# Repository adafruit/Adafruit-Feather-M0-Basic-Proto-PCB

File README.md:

## Adafruit Feather M0 Basic Proto PCB
<a href="http://www.adafruit.com/products/2772"><br/>
Click here to purchase one from the Adafruit shop</a>

The Feather M0 has an ATSAMD21G18 ARM Cortex M0 processor, clocked at 48 MHz and at 3.3V logic, the same one used in the Arduino Zero. This chip has a whopping 256K of FLASH (8x more than the Atmega328 or 32u4) and 32K of RAM (16x as much)! This chip comes with built in USB so it has USB-to-Serial program & debug capability built in with no need for an FTDI-like chip.

To make it easy to use for portable projects, we added a connector for any of our 3.7V Lithium polymer batteries and built in battery charging. You don't need a battery, it will run just fine straight from the micro USB connector. But, if you do have a battery, you can take it on the go, then plug in the USB to recharge. The Feather will automatically switch over to USB power when its available. We also tied the battery thru a divider to an analog pin, so you can measure and monitor the battery voltage to detect when you need a recharge.

PCB files for the Adafruit Feather M0 Basic Proto. The format is EagleCAD schematic and board layout
- https://www.adafruit.com/product/2772

### License

Adafruit invests time and resources providing this open source design, please support Adafruit and open-source hardware by purchasing products from [Adafruit](https://www.adafruit.com)!

All text above must be included in any redistribution

Designed by Limor Fried/Ladyada for Adafruit Industries.
Creative Commons Attribution/Share-Alike, all text above must be included in any redistribution. 
See license.txt for additional information.

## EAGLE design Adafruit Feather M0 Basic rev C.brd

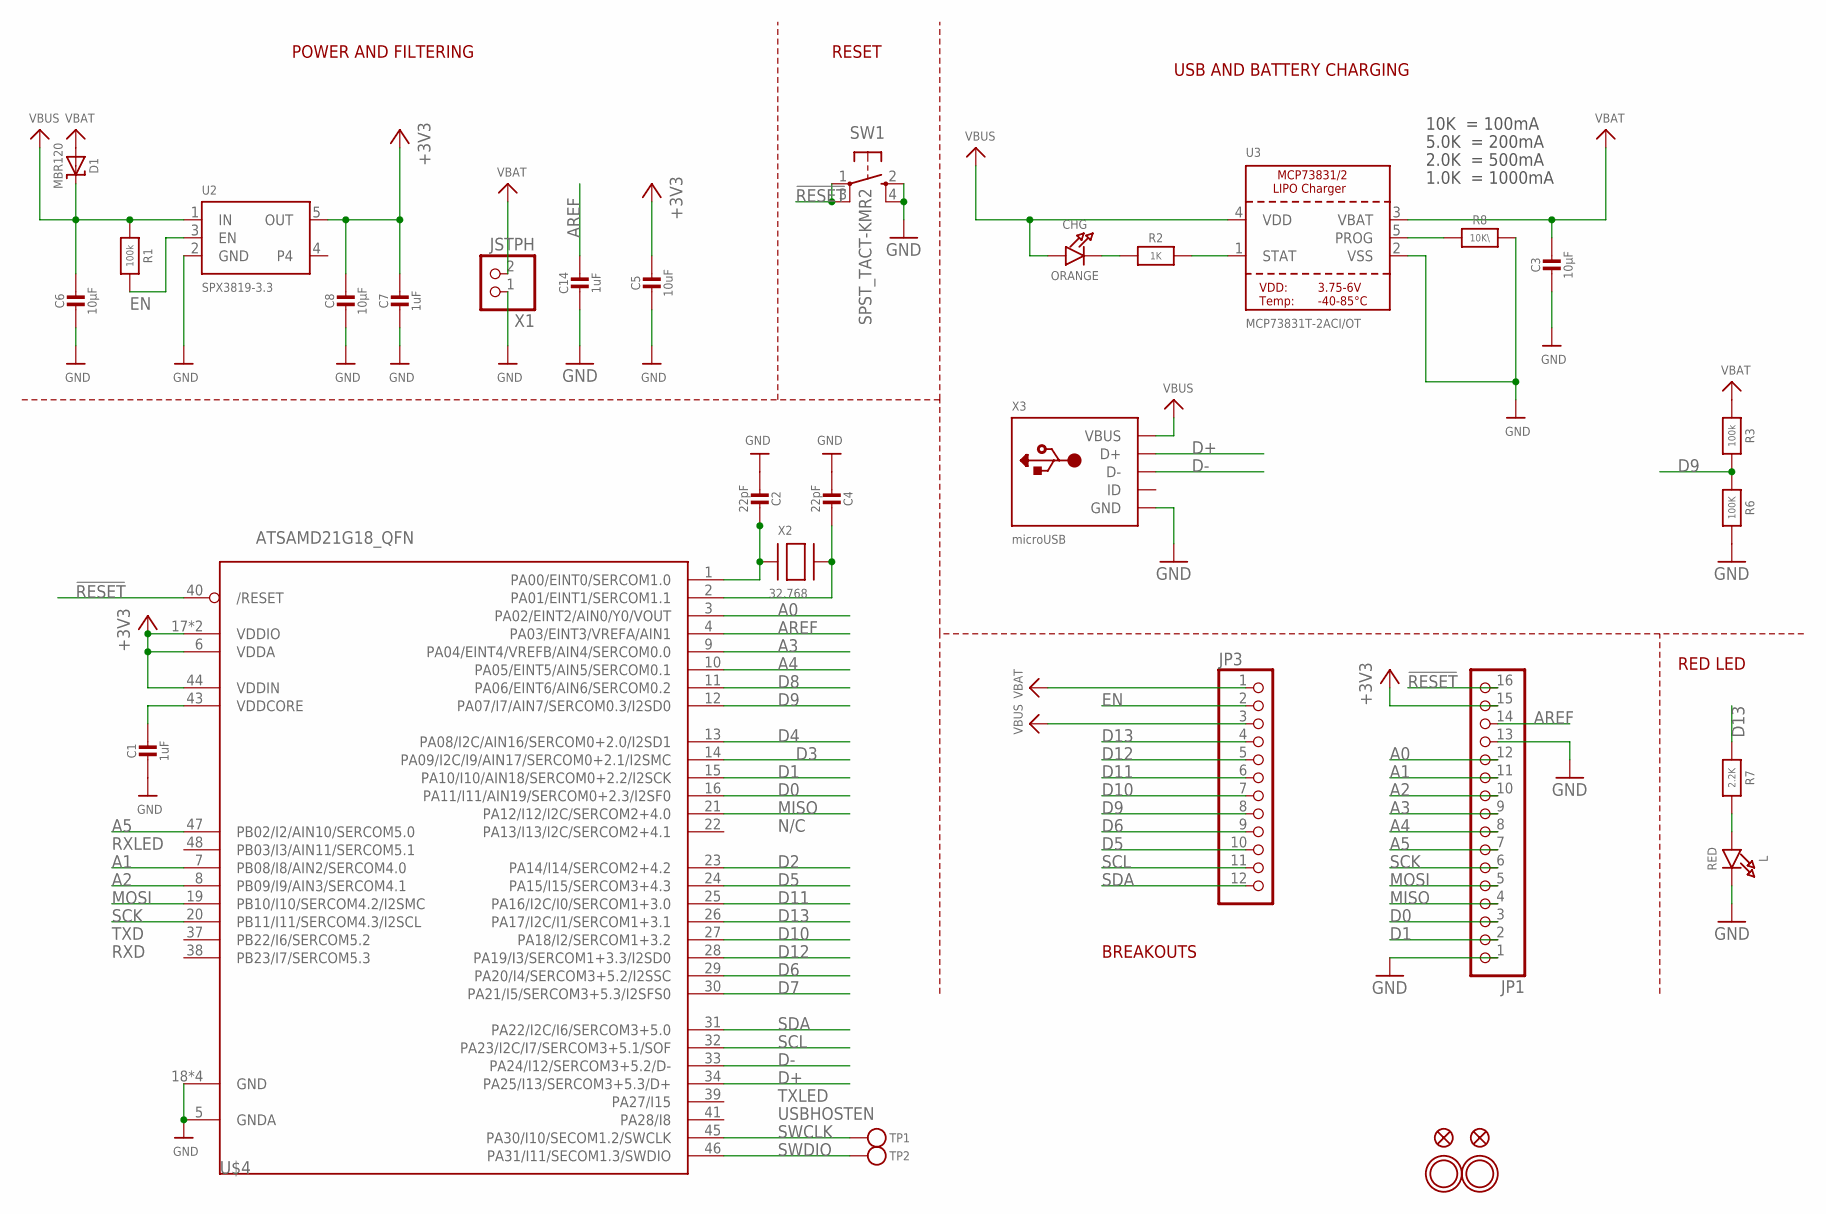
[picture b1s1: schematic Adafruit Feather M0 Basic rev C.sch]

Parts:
C1, C7, C14: 1uF; 0603-NO
C2, C4: 22pF; 0603-NO
C3, C6, C8: 10µF; 0805-NO
C5: 10uF; 0805-NO
CHG: ORANGE; CHIPLED_0805_NOOUTLINE
D1: MBR120; SOD-123
JP1: HEADER-1X16ROUND; 1X16_ROUND
JP3: HEADER-1X12; 1X12_ROUND
L: RED; CHIPLED_0805_NOOUTLINE
R1, R3: 100k; 0603-NO
R2: 1K; 0603-NO
R6: 100K; 0603-NO
R7: 2.2K; 0603-NO
R8: 10K\; 0603-NO
SW1: SPST_TACT-KMR2; KMR2
TP1, TP2: TESTPOINTROUND1.5MM; TESTPOINT_ROUND_1.5MM
U2: SPX3819-3.3; SOT23-5
U3: MCP73831T-2ACI/OT; SOT23-5
U$4: ATSAMD21G18_QFN; TQFN48_7MM
U$31, U$32: MOUNTINGHOLE2.5; MOUNTINGHOLE_2.5_PLATED
U$34, U$35: FIDUCIAL""; FIDUCIAL_1MM
X1: JSTPH; JSTPH2
X2: 32.768; XTAL3215
X3: microUSB; 4UCONN_20329_V2

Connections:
!RESET: JP1.16, SW1.1, SW1.3 (P1), U$4.40 (/RESET)
+3V3: C5.1, C7.1, C8.1, JP1.15, U2.5 (OUT), U$4.6 (VDDA), U$4.17 (VDDIO), U$4.36 (VDDIO), U$4.44 (VDDIN)
A0: JP1.12, U$4.3 (PA02/EINT2/AIN0/Y0/VOUT)
A1: JP1.11, U$4.7 (PB08/I8/AIN2/SERCOM4.0)
A2: JP1.10, U$4.8 (PB09/I9/AIN3/SERCOM4.1)
A3: JP1.9, U$4.9 (PA04/EINT4/VREFB/AIN4/SERCOM0.0)
A4: JP1.8, U$4.10 (PA05/EINT5/AIN5/SERCOM0.1)
A5: JP1.7, U$4.47 (PB02/I2/AIN10/SERCOM5.0)
AREF: C14.1, JP1.14, U$4.4 (PA03/EINT3/VREFA/AIN1)
D0: JP1.3, U$4.16 (PA11/I11/AIN19/SERCOM0+2.3/I2SF0)
D1: JP1.2, U$4.15 (PA10/I10/AIN18/SERCOM0+2.2/I2SCK)
D2: U$4.23 (PA14/I14/SERCOM2+4.2)
D3: U$4.14 (PA09/I2C/I9/AIN17/SERCOM0+2.1/I2SMC)
D4: U$4.13 (PA08/I2C/AIN16/SERCOM0+2.0/I2SD1)
D5: JP3.10, U$4.24 (PA15/I15/SERCOM3+4.3)
D6: JP3.9, U$4.29 (PA20/I4/SERCOM3+5.2/I2SSC)
D7: U$4.30 (PA21/I5/SERCOM3+5.3/I2SFS0)
D8: U$4.11 (PA06/EINT6/AIN6/SERCOM0.2)
D9: JP3.8, R3.2, R6.1, U$4.12 (PA07/I7/AIN7/SERCOM0.3/I2SD0)
D10: JP3.7, U$4.27 (PA18/I2/SERCOM1+3.2)
D11: JP3.6, U$4.25 (PA16/I2C/I0/SERCOM1+3.0)
D12: JP3.5, U$4.28 (PA19/I3/SERCOM1+3.3/I2SD0)
D13: JP3.4, R7.1, U$4.26 (PA17/I2C/I1/SERCOM1+3.1)
D+: U$4.34 (PA25/I13/SERCOM3+5.3/D+), X3.D+
D-: U$4.33 (PA24/I12/SERCOM3+5.2/D-), X3.D-
EN: JP3.2, R1.2, U2.3 (EN)
GND: C1.2, C2.2, C3.2, C4.2, C5.2, C6.2, C7.2, C8.2, C14.2, JP1.1, JP1.13, L.C, R6.2, R8.2, SW1.2 (S), SW1.4 (S1), U2.2 (GND), U3.2 (VSS), U$4.5 (GNDA), U$4.18 (GND), U$4.35 (GND), U$4.42 (GND), U$4.THERMAL (GND), X1.1, X3.BASE@1 (GND), X3.BASE@2 (GND), X3.GND, X3.SPRT@1 (GND), X3.SPRT@2 (GND), X3.SPRT@3 (GND), X3.SPRT@4 (GND)
MISO: JP1.4, U$4.21 (PA12/I12/I2C/SERCOM2+4.0)
MOSI: JP1.5, U$4.19 (PB10/I10/SERCOM4.2/I2SMC)
unnamed: CHG.C, R2.1
unnamed: L.A, R7.2
unnamed: R2.2, U3.1 (STAT)
unnamed: R8.1, U3.5 (PROG)
unnamed: C2.1, U$4.1 (PA00/EINT0/SERCOM1.0), X2.P$1
unnamed: C4.1, U$4.2 (PA01/EINT1/SERCOM1.1), X2.P$2
SCK: JP1.6, U$4.20 (PB11/I11/SERCOM4.3/I2SCL)
SCL: JP3.11, U$4.32 (PA23/I2C/I7/SERCOM3+5.1/SOF)
SDA: JP3.12, U$4.31 (PA22/I2C/I6/SERCOM3+5.0)
SWCLK: TP1.P$1, U$4.45 (PA30/I10/SECOM1.2/SWCLK)
SWDIO: TP2.P$1, U$4.46 (PA31/I11/SECOM1.3/SWDIO)
VBAT: C3.1, D1.A, JP3.1, R3.1, U3.3 (VBAT), X1.2
VBUS: C6.1, CHG.A, D1.C, JP3.3, R1.1, U2.1 (IN), U3.4 (VDD), X3.VBUS
VDDCORE: C1.1, U$4.43 (VDDCORE)

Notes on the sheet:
POWER AND FILTERING
RESET
10K = 100mA
5.0K = 200mA
2.0K = 500mA
1.0K = 1000mA
N/C
TXLED
USBHOSTEN
RXLED
TXD
RXD
USB AND BATTERY CHARGING
BREAKOUTS
RED LED

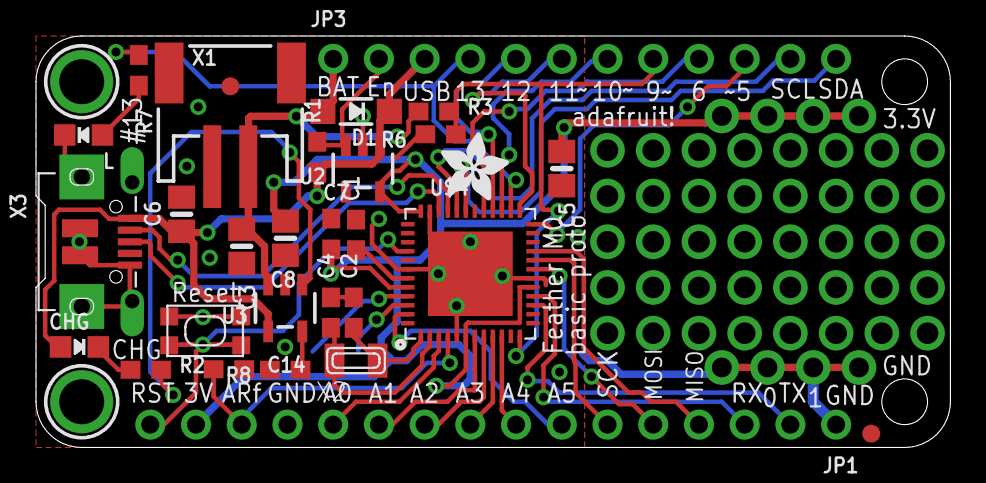
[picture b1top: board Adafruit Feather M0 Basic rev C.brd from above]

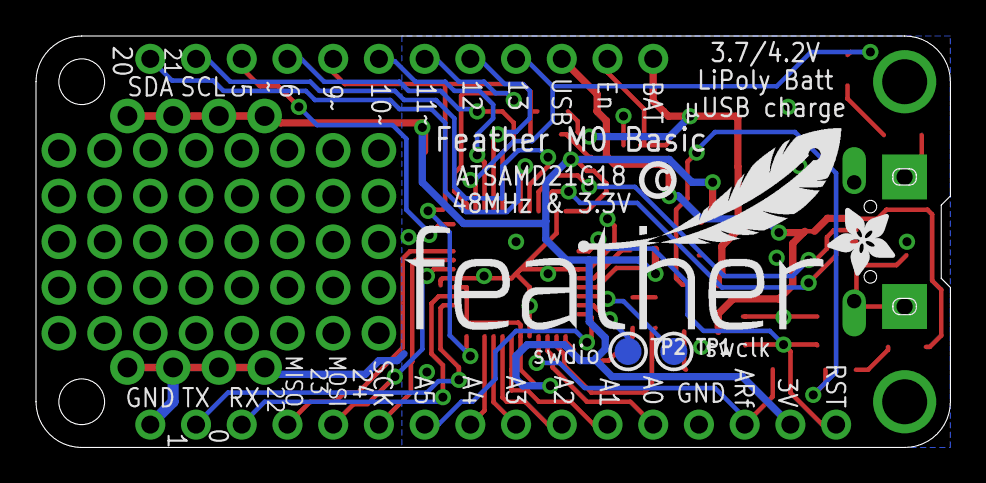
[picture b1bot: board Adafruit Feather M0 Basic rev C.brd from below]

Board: 2 copper layers, 50.8 x 22.9 mm, 37 parts (5 on the bottom side), 38 nets.

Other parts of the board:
U$7, U$12: ADAFRUIT_3.5MM
U$9: FEATHERLOGO
U$13: PCBFEAT-REV-040

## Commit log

2015-12-08 init pcb
2015-12-08 fix url!
2016-01-12 bootloader for atsamd using adafruit vid/pid & pulsing LED
2022-04-19 Added PrettyPins

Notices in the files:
parts and their libraries:
microbuilder: This work is placed in the public domain, and may be freely used for commercial and non-commercial work with the following conditions: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
